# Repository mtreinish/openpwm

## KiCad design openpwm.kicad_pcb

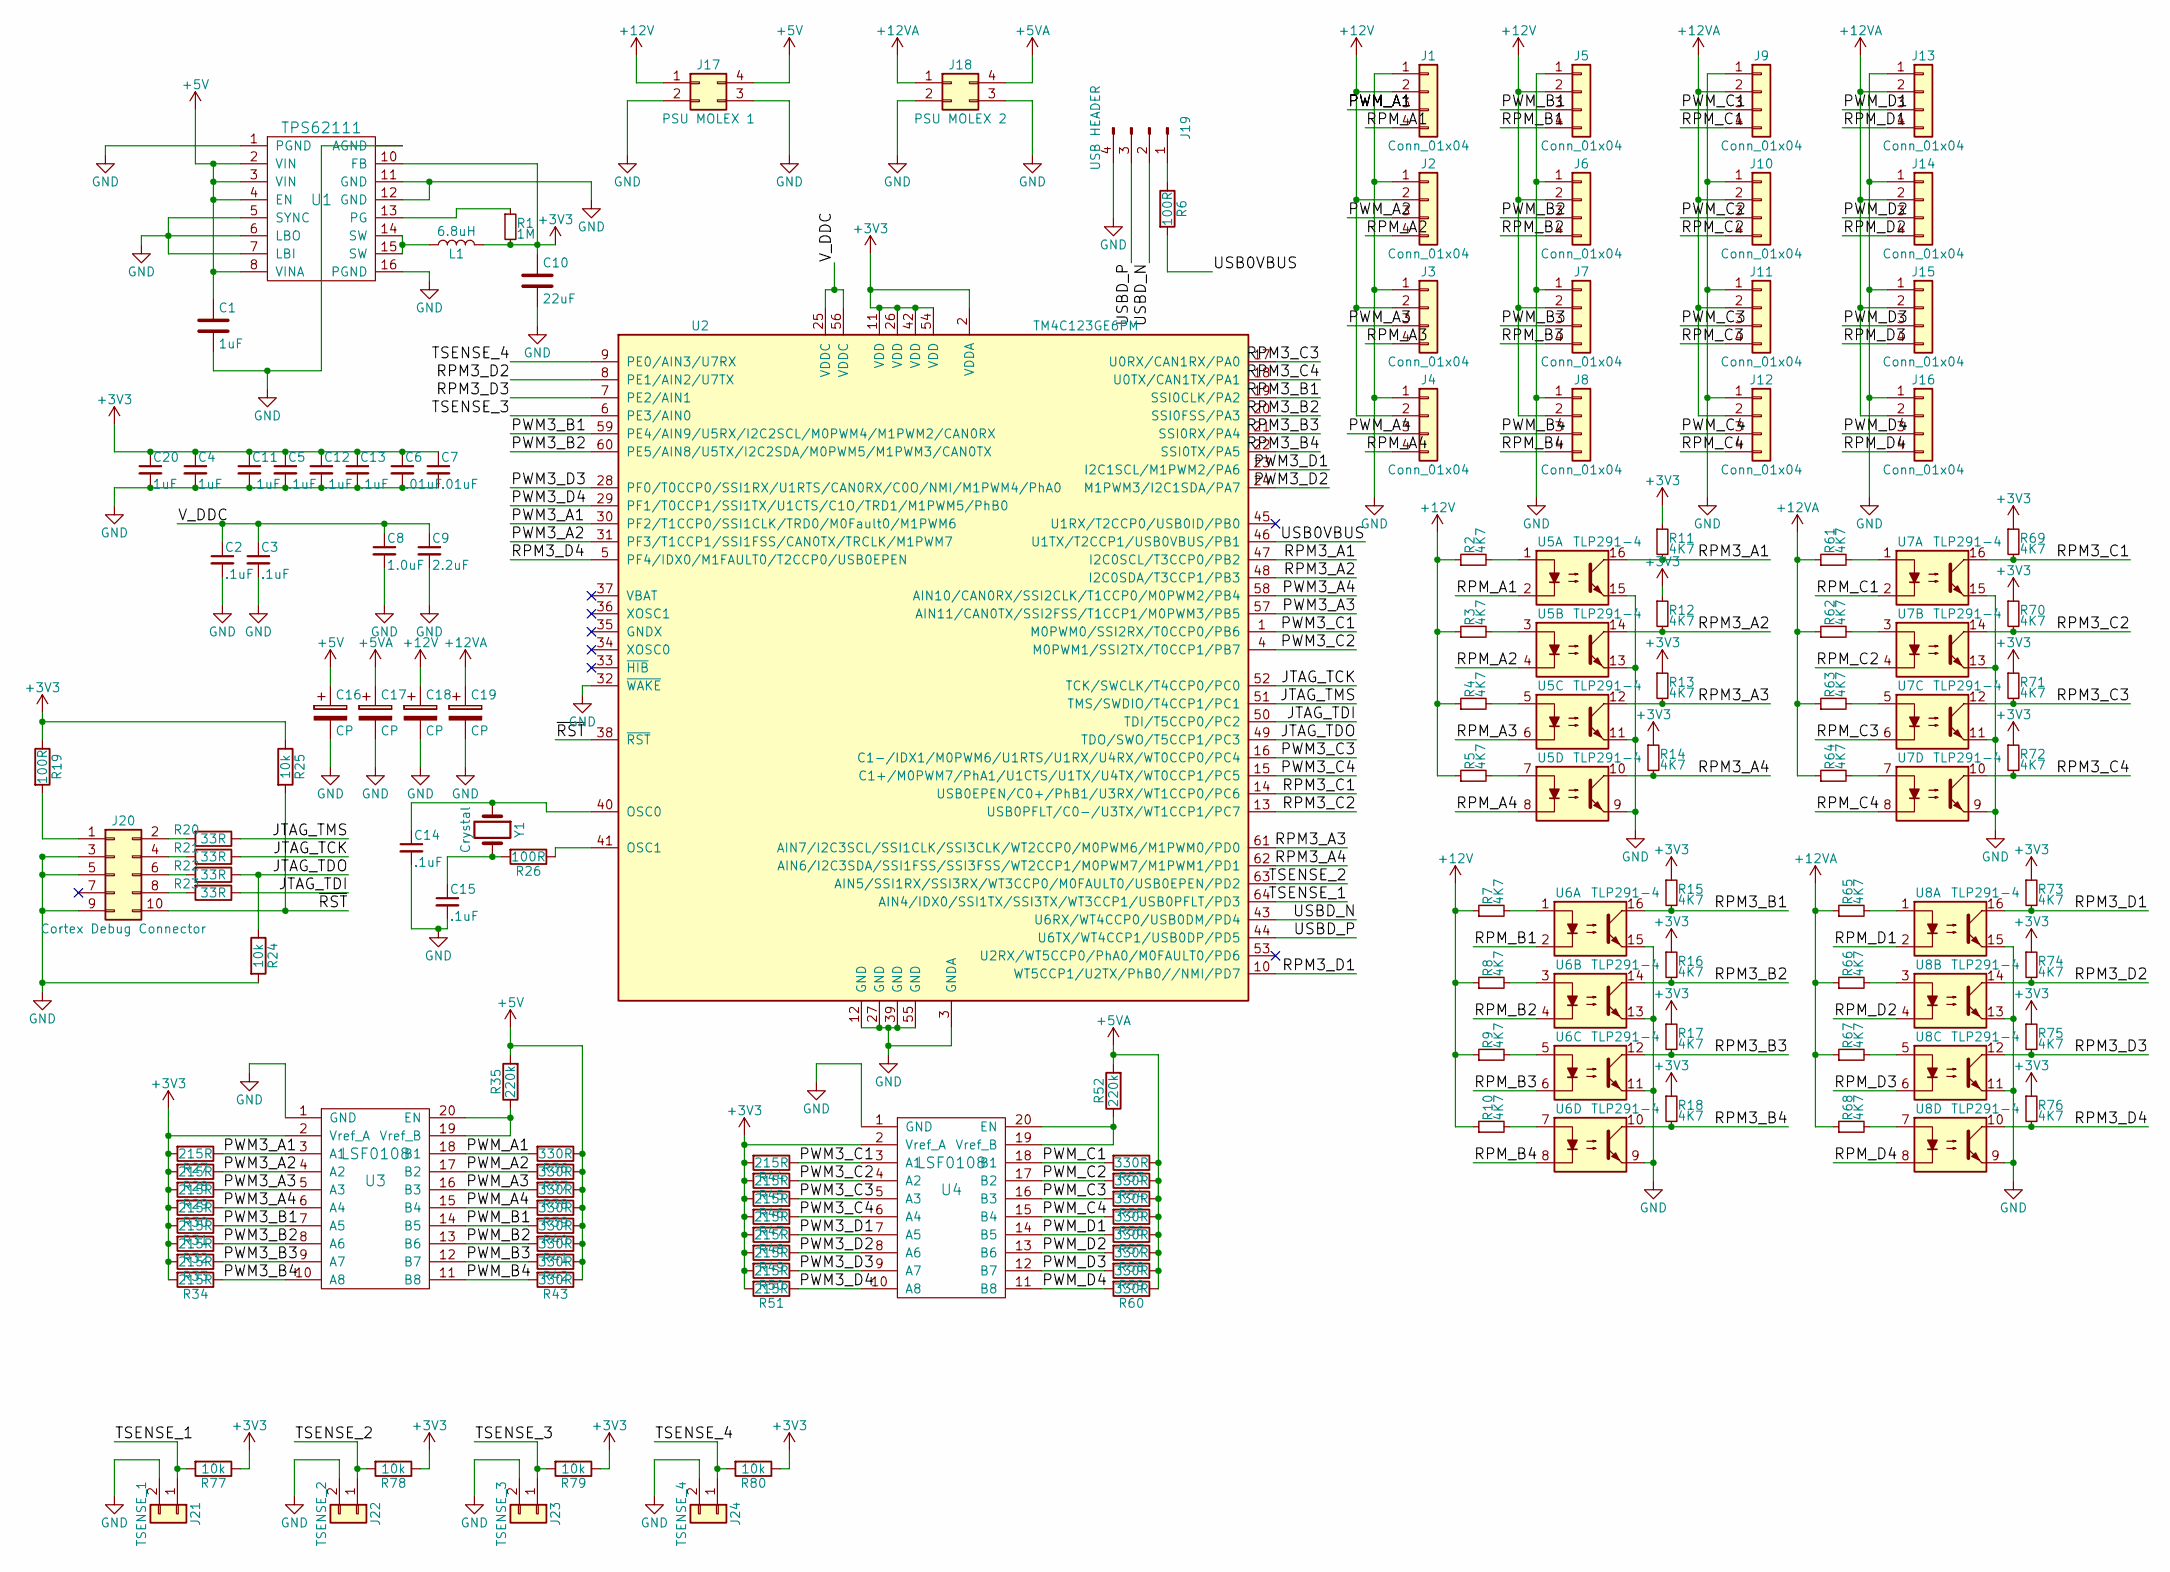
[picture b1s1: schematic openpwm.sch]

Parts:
C1, C4, C20: 1uF; C_0603_HandSoldering
C2, C3, C5, C11, C12, C13, C14, C15: .1uF; C_0603_HandSoldering
C6, C7: .01uF; C_0603_HandSoldering
C8: 1.0uF; C_0603_HandSoldering
C9: 2.2uF; C_0603_HandSoldering
C10: 22uF; R_0603_HandSoldering
C16, C17, C18, C19: CP; CP_Elec_5x4.5
J1, J2, J3, J4, J5, J6, J7, J8, J9, J10, J11, J12, J13, J14, J15, J16: Conn_01x04; Molex_KK-6410-04_04x2.54mm_Straight
J17: PSU MOLEX 1; conn_hdd_15-24-4449
J18: PSU MOLEX 2; conn_hdd_15-24-4449
J19: USB HEADER; Pin_Header_Straight_1x04_Pitch2.54mm
J20: Cortex Debug Connector; CORTEX_DEBUG_CONNECTOR
J21: TSENSE_1; Pin_Header_Straight_1x02_Pitch2.54mm
J22: TSENSE_2; Pin_Header_Straight_1x02_Pitch2.54mm
J23: TSENSE_3; Pin_Header_Straight_1x02_Pitch2.54mm
J24: TSENSE_4; Pin_Header_Straight_1x02_Pitch2.54mm
L1: 6.8uH; L_0603_HandSoldering
R1: 1M; R_0603_HandSoldering
R2, R3, R4, R5, R7, R8, R9, R10, R11, R12, R13, R14, R15, R16, R17, R18, R61, R62, R63, R64, R65, R66, R67, R68, R69, R70, R71, R72, R73, R74, R75, R76: 4K7; R_0603_HandSoldering
R6, R19, R26: 100R; R_0603_HandSoldering
R20, R21, R22, R23: 33R; R_0603_HandSoldering
R24, R25, R77, R78, R79, R80: 10k; R_0603_HandSoldering
R27, R28, R29, R30, R31, R32, R33, R34, R44, R45, R46, R47, R48, R49, R50, R51: 215R; R_0603_HandSoldering
R35, R52: 220k; R_0603_HandSoldering
R36, R37, R38, R39, R40, R41, R42, R43, R53, R54, R55, R56, R57, R58, R59, R60: 330R; R_0603_HandSoldering
U1: TPS62111; QFN-16-1EP_4x4mm_Pitch0.65mm
U2: TM4C123GE6PM; LQFP-64_10x10mm_Pitch0.5mm
U3, U4: LSF0108; SSOP-20
U5, U6, U7, U8: TLP291-4; SOIC-16W_7.5x10.3mm_Pitch1.27mm
Y1: Crystal; Crystal_SMD_5032-2pin_5.0x3.2mm_HandSoldering

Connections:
+3V3: C4.1, C5.1, C6.1, C7.1, C10.1, C11.1, C12.1, C13.1, C20.1, L1.2, R1.2, R11.1, R12.1, R13.1, R14.1, R15.1, R16.1, R17.1, R18.1, R19.1, R25.1, R27.2, R28.2, R29.2, R30.2, R31.2, R32.2, R33.2, R34.2, R44.2, R45.2, R46.2, R47.2, R48.2, R49.2, R50.2, R51.2, R69.1, R70.1, R71.1, R72.1, R73.1, R74.1, R75.1, R76.1, R77.1, R78.1, R79.1, R80.1, U1.10 (FB), U2.2 (VDDA), U2.11 (VDD), U2.26 (VDD), U2.42 (VDD), U2.54 (VDD), U3.2 (Vref_A), U4.2 (Vref_A)
+5V: C1.1, C16.1, J17.4, R35.2, R36.1, R37.1, R38.1, R39.1, R40.1, R41.1, R42.1, R43.1, U1.2 (VIN), U1.3 (VIN), U1.4 (EN), U1.8 (VINA)
+5VA: C17.1, J18.4, R52.2, R53.1, R54.1, R55.1, R56.1, R57.1, R58.1, R59.1, R60.1
+12V: C18.1, J1.2, J2.2, J3.2, J4.2, J5.2, J6.2, J7.2, J8.2, J17.1, R2.1, R3.1, R4.1, R5.1, R7.1, R8.1, R9.1, R10.1
+12VA: C19.1, J9.2, J10.2, J11.2, J12.2, J13.2, J14.2, J15.2, J16.2, J18.1, R61.1, R62.1, R63.1, R64.1, R65.1, R66.1, R67.1, R68.1
/JTAG_TCK: R21.1, U2.52 (TCK/SWCLK/T4CCP0/PC0)
/JTAG_TDI: R23.1, U2.50 (TDI/T5CCP0/PC2)
/JTAG_TDO: R22.1, R24.1, U2.49 (TDO/SWO/T5CCP1/PC3)
/JTAG_TMS: R20.1, U2.51 (TMS/SWDIO/T4CCP1/PC1)
/PWM3_A1: R27.1, U2.30 (PF2/T1CCP0/SSI1CLK/TRD0/M0Fault0/M1PWM6), U3.3 (A1)
/PWM3_A2: R28.1, U2.31 (PF3/T1CCP1/SSI1FSS/CAN0TX/TRCLK/M1PWM7), U3.4 (A2)
/PWM3_A3: R29.1, U2.57 (AIN11/CAN0TX/SSI2FSS/T1CCP1/M0PWM3/PB5), U3.5 (A3)
/PWM3_A4: R30.1, U2.58 (AIN10/CAN0RX/SSI2CLK/T1CCP0/M0PWM2/PB4), U3.6 (A4)
/PWM3_B1: R31.1, U2.59 (PE4/AIN9/U5RX/I2C2SCL/M0PWM4/M1PWM2/CAN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), U3.7 (A5)
/PWM3_B2: R32.1, U2.60 (PE5/AIN8/U5TX/I2C2SDA/M0PWM5/M1PWM3/CAN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), U3.8 (A6)
/PWM3_B3: R33.1, U3.9 (A7)
/PWM3_B4: R34.1, U3.10 (A8)
/PWM3_C1: R44.1, U2.1 (M0PWM0/SSI2RX/T0CCP0/PB6), U4.3 (A1)
/PWM3_C2: R45.1, U2.4 (M0PWM1/SSI2TX/T0CCP1/PB7), U4.4 (A2)
/PWM3_C3: R46.1, U2.16 (C1-/IDX1/M0PWM6/U1RTS/U1RX/U4RX/WT0CCP0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), U4.5 (A3)
/PWM3_C4: R47.1, U2.15 (C1+/M0PWM7/PhA1/U1CTS/U1TX/U4TX/WT0CCP1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), U4.6 (A4)
/PWM3_D1: R48.1, U2.23 (I2C1SCL/M1PWM2/PA6), U4.7 (A5)
/PWM3_D2: R49.1, U2.24 (M1PWM3/I2C1SDA/PA7), U4.8 (A6)
/PWM3_D3: R50.1, U2.28 (PF0/T0CCP0/SSI1RX/U1RTS/CAN0RX/C0O/NMI/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), U4.9 (A7)
/PWM3_D4: R51.1, U2.29 (PF1/T0CCP1/SSI1TX/U1CTS/C1O/TRD1/M1PWM5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), U4.10 (A8)
/PWM_A1: J1.3, R36.2, U3.18 (B1)
/PWM_A2: J2.3, R37.2, U3.17 (B2)
/PWM_A3: J3.3, R38.2, U3.16 (B3)
/PWM_A4: J4.3, R39.2, U3.15 (B4)
/PWM_B1: J5.3, R40.2, U3.14 (B5)
/PWM_B2: J6.3, R41.2, U3.13 (B6)
/PWM_B3: J7.3, R42.2, U3.12 (B7)
/PWM_B4: J8.3, R43.2, U3.11 (B8)
/PWM_C1: J9.3, R53.2, U4.18 (B1)
/PWM_C2: J10.3, R54.2, U4.17 (B2)
/PWM_C3: J11.3, R55.2, U4.16 (B3)
/PWM_C4: J12.3, R56.2, U4.15 (B4)
/PWM_D1: J13.3, R57.2, U4.14 (B5)
/PWM_D2: J14.3, R58.2, U4.13 (B6)
/PWM_D3: J15.3, R59.2, U4.12 (B7)
/PWM_D4: J16.3, R60.2, U4.11 (B8)
/RPM3_A1: R11.2, U2.47 (I2C0SCL/T3CCP0/PB2), U5.16
/RPM3_A2: R12.2, U2.48 (I2C0SDA/T3CCP1/PB3), U5.14
/RPM3_A3: R13.2, U2.61 (AIN7/I2C3SCL/SSI1CLK/SSI3CLK/WT2CCP0/M0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), U5.12
/RPM3_A4: R14.2, U2.62 (AIN6/I2C3SDA/SSI1FSS/SSI3FSS/WT2CCP1/M0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), U5.10
/RPM3_B1: R15.2, U2.19 (SSI0CLK/PA2), U6.16
/RPM3_B2: R16.2, U2.20 (SSI0FSS/PA3), U6.14
/RPM3_B3: R17.2, U2.21 (SSI0RX/PA4), U6.12
/RPM3_B4: R18.2, U2.22 (SSI0TX/PA5), U6.10
/RPM3_C1: R69.2, U2.14 (USB0EPEN/C0+/PhB1/U3RX/WT1CCP0/PC6), U7.16
/RPM3_C2: R70.2, U2.13 (USB0PFLT/C0-/U3TX/WT1CCP1/PC7), U7.14
/RPM3_C3: R71.2, U2.17 (U0RX/CAN1RX/PA0), U7.12
/RPM3_C4: R72.2, U2.18 (U0TX/CAN1TX/PA1), U7.10
/RPM3_D1: R73.2, U2.10 (WT5CCP1/U2TX/PhB0//NMI/PD7), U8.16
/RPM3_D2: R74.2, U2.8 (PE1/AIN2/U7TX), U8.14
/RPM3_D3: R75.2, U2.7 (PE2/AIN1), U8.12
/RPM3_D4: R76.2, U2.5 (PF4/IDX0/M1FAULT0/T2CCP0/USB0EPEN), U8.10
/RPM_A1: J1.4, U5.2
/RPM_A2: J2.4, U5.4
/RPM_A3: J3.4, U5.6
/RPM_A4: J4.4, U5.8
/RPM_B1: J5.4, U6.2
/RPM_B2: J6.4, U6.4
/RPM_B3: J7.4, U6.6
/RPM_B4: J8.4, U6.8
/RPM_C1: J9.4, U7.2
/RPM_C2: J10.4, U7.4
/RPM_C3: J11.4, U7.6
/RPM_C4: J12.4, U7.8
/RPM_D1: J13.4, U8.2
/RPM_D2: J14.4, U8.4
/RPM_D3: J15.4, U8.6
/RPM_D4: J16.4, U8.8
/TSENSE_1: J21.1, R77.2, U2.64 (AIN4/IDX0/SSI1TX/SSI3TX/WT3CCP1/USB0PFL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)
/TSENSE_2: J22.1, R78.2, U2.63 (AIN5/SSI1RX/SSI3RX/WT3CCP0/M0FAULT0/USB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)
/TSENSE_3: J23.1, R79.2, U2.6 (PE3/AIN0)
/TSENSE_4: J24.1, R80.2, U2.9 (PE0/AIN3/U7RX)
/USB0VBUS: R6.2, U2.46 (U1TX/T2CCP1/USB0VBUS/PB1)
/USBD_N: J19.2, U2.43 (U6RX/WT4CCP0/USB0DM/PD4)
/USBD_P: J19.3, U2.44 (U6TX/WT4CCP1/USB0DP/PD5)
/V_DDC: C2.1, C3.1, C8.1, C9.1, U2.25 (VDDC), U2.56 (VDDC)
/~RST~: J20.10, R25.2, U2.38 (~RST~)
GND: C1.2, C2.2, C3.2, C4.2, C5.2, C6.2, C7.2, C8.2, C9.2, C10.2, C11.2, C12.2, C13.2, C14.2, C15.2, C16.2, C17.2, C18.2, C19.2, C20.2, J1.1, J2.1, J3.1, J4.1, J5.1, J6.1, J7.1, J8.1, J9.1, J10.1, J11.1, J12.1, J13.1, J14.1, J15.1, J16.1, J17.2, J17.3, J18.2, J18.3, J19.4, J20.3, J20.5, J20.9, J21.2, J22.2, J23.2, J24.2, R24.2, U1.1 (PGND), U1.5 (SYNC), U1.6 (LBO), U1.7 (LBI), U1.11 (GND), U1.12 (GND), U1.16 (PGND), U1.~ (AGND), U2.3 (GNDA), U2.12 (GND), U2.27 (GND), U2.32 (~WAKE~), U2.39 (GND), U2.55 (GND), U3.1 (GND), U4.1 (GND), U5.9, U5.11, U5.13, U5.15, U6.9, U6.11, U6.13, U6.15, U7.9, U7.11, U7.13, U7.15, U8.9, U8.11, U8.13, U8.15
unnamed: C14.1, U2.40 (OSC0), Y1.1
unnamed: C15.1, R26.2, Y1.2
unnamed: J19.1, R6.1
unnamed: J20.1, R19.2
unnamed: J20.2, R20.2
unnamed: J20.4, R21.2
unnamed: J20.6, R22.2
unnamed: J20.8, R23.2
unnamed: L1.1, U1.14 (SW), U1.15 (SW)
unnamed: R1.1, U1.13 (PG)
unnamed: R2.2, U5.1
unnamed: R3.2, U5.3
unnamed: R4.2, U5.5
unnamed: R5.2, U5.7
unnamed: R7.2, U6.1
unnamed: R8.2, U6.3
unnamed: R9.2, U6.5
unnamed: R10.2, U6.7
unnamed: R26.1, U2.41 (OSC1)
unnamed: R35.1, U3.19 (Vref_B), U3.20 (EN)
unnamed: R52.1, U4.19 (Vref_B), U4.20 (EN)
unnamed: R61.2, U7.1
unnamed: R62.2, U7.3
unnamed: R63.2, U7.5
unnamed: R64.2, U7.7
unnamed: R65.2, U8.1
unnamed: R66.2, U8.3
unnamed: R67.2, U8.5
unnamed: R68.2, U8.7

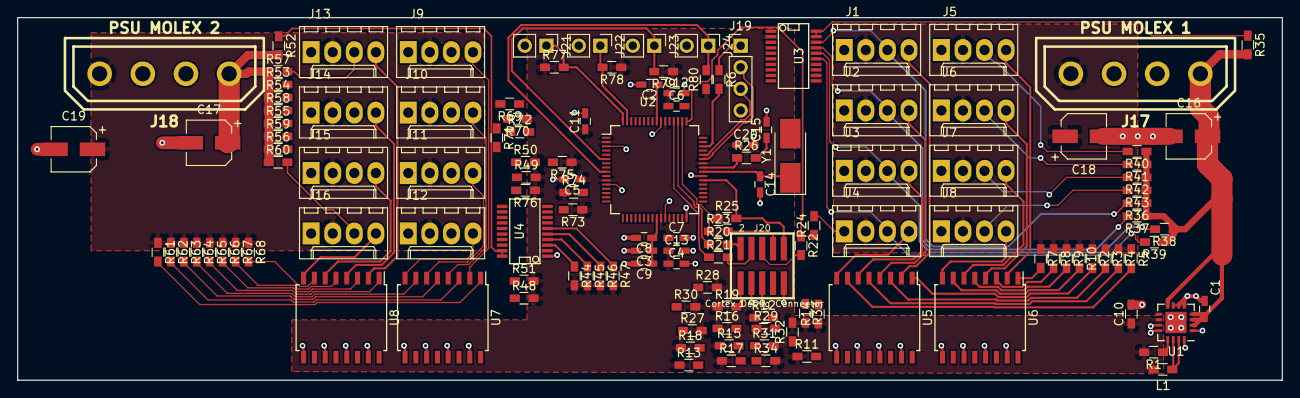
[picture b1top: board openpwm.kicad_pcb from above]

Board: 2 copper layers, 148.8 x 42.7 mm, 134 parts (0 on the bottom side), 112 nets.

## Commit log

2018-01-02 Initial commit
    This is the initial commit for the project. The schematic is sorta done
    (although more work is likely needed) and the pcb is barely even
    started. Just pushing at this point to start sharing the initial design.
2018-01-02 Start the PCB layout
    This commit starts the PCB layout. There is still a long way to go;
    just using this as checkpoint.
2018-01-04 70 nets to go
2018-01-06 Fix optocoupler schematic
